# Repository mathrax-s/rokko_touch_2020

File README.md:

# rokko_touch_2020
EAGLE and KiCad files (PSoC4 flexible touch sensor)

</img>

</img>

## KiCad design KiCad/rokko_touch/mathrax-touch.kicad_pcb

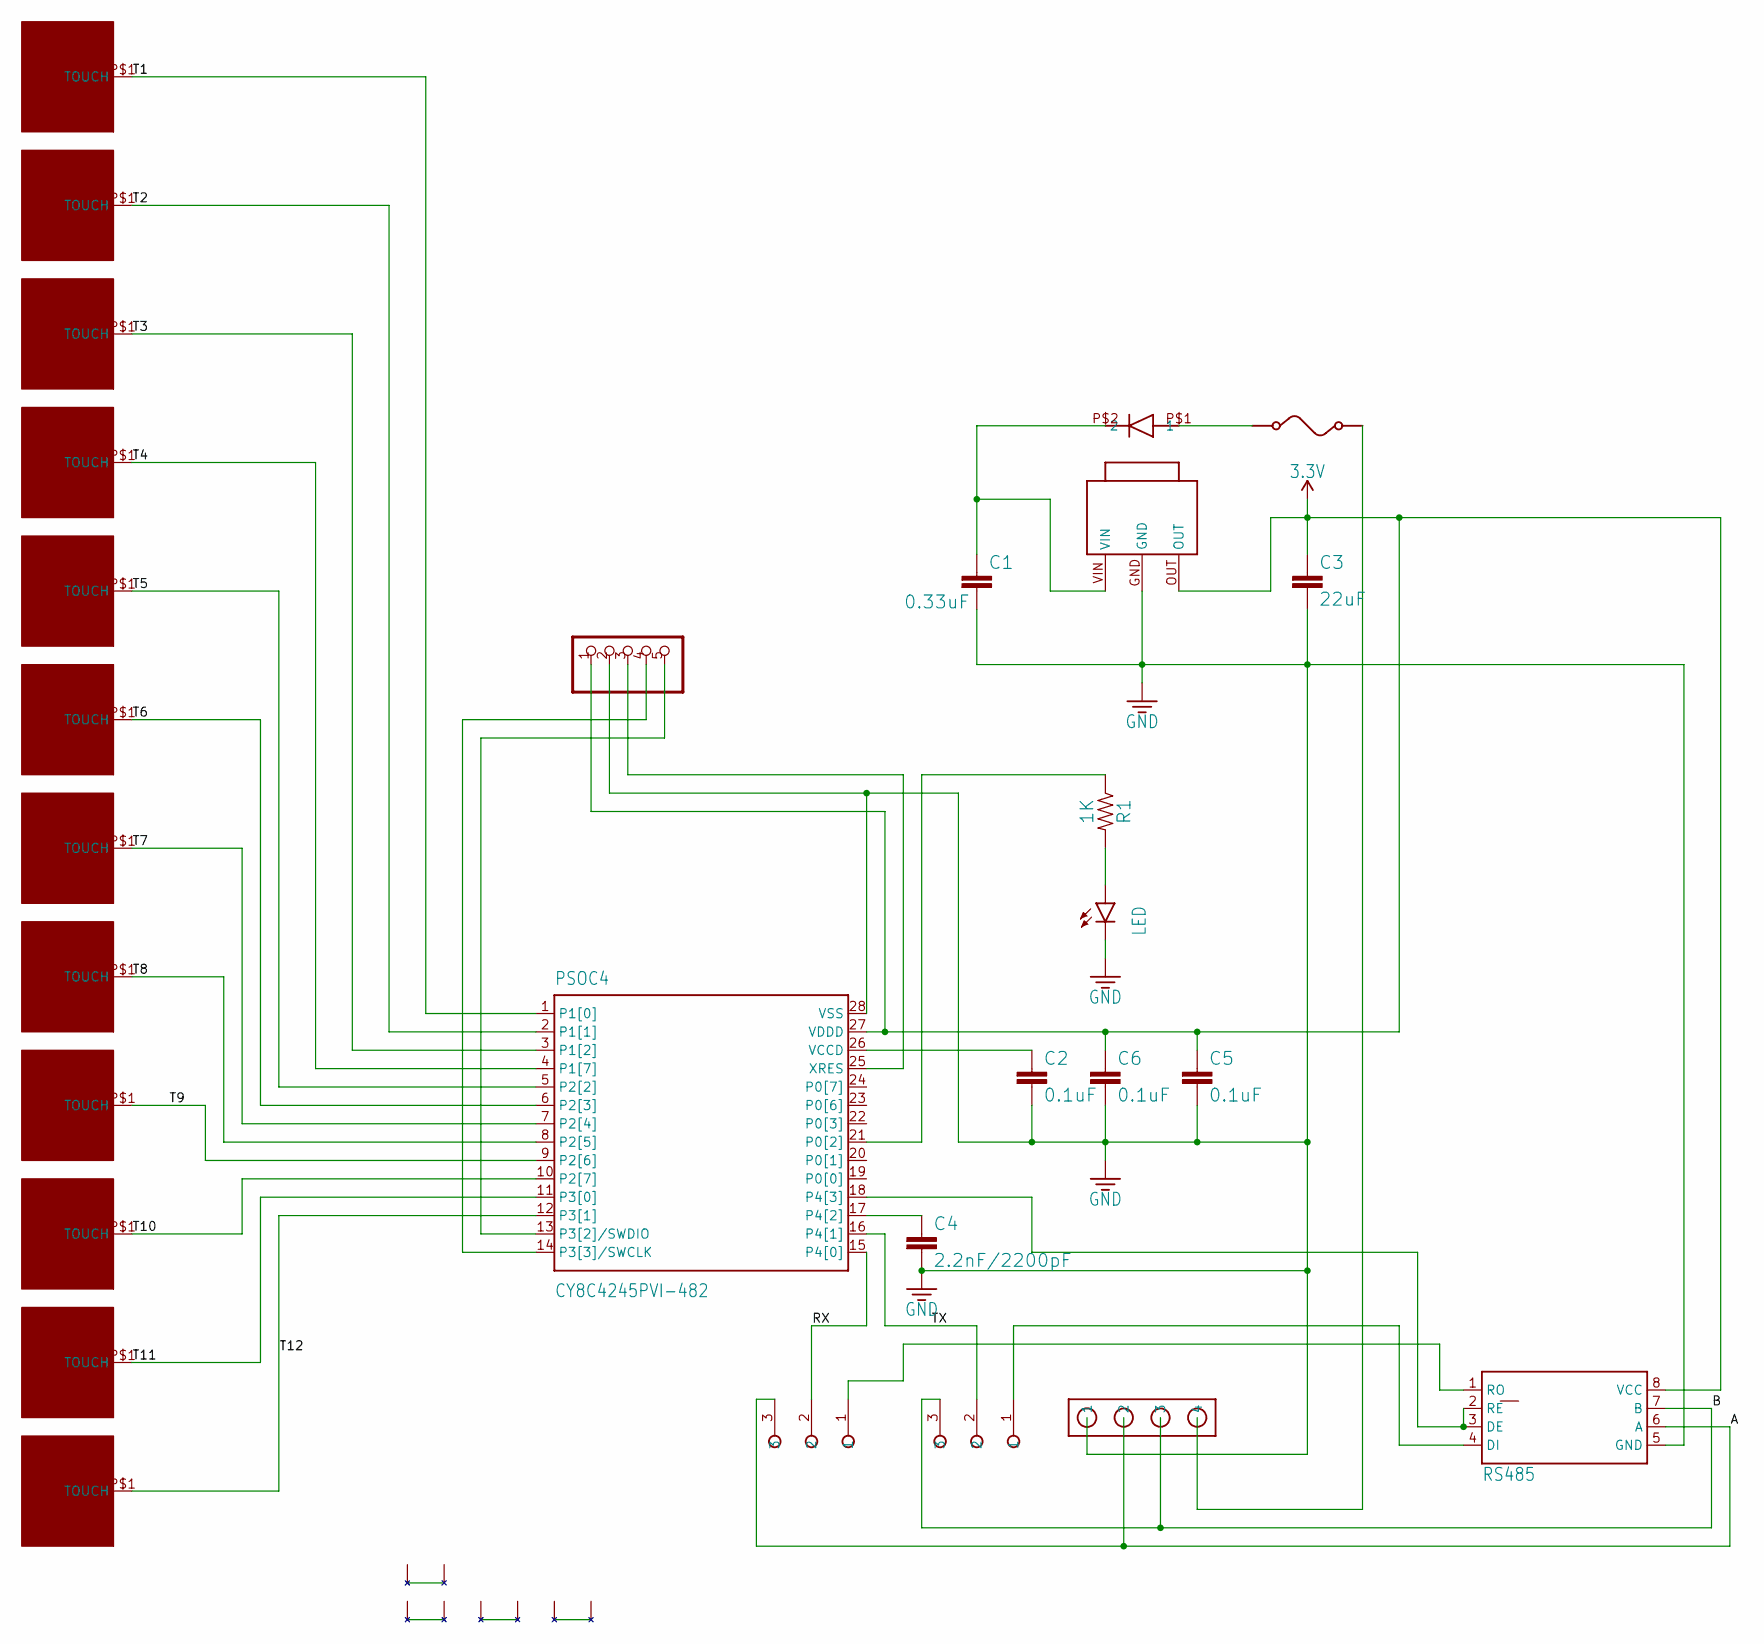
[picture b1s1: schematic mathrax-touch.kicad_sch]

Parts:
C1: 0.33uF; 3216
C2, C5, C6: 0.1uF; 0603
C3: 22uF; 1210
C4: 2.2nF/2200pF; 0603
F1: POLY-SWITCH-HUSE; RESETABLE-HUES
LED0: LED; CHIPLED_0805
PSOC4: CY8C4245PVI-482; SSOP28
R1: 1K; 0603
RS485: RS485; SOIC127P600X175-8N
U$1: PINHEADER-5; PINHEADER-5L
U$2: TOUCH-PTN-3; TOUCH-PTN3
U$3, U$4, U$5, U$6, U$7, U$8, U$9, U$18, U$19, U$20: TOUCH-PTN-2; TOUCH-PTN2
U$11: EH4-UART
U$13: REGULATOR-TO252-3; BA33BC0FP
U$21: TOUCH-PTN-1; TOUCH-PTN1
U$22: DIODE-SS2040L
U$23, U$24: JUMPER
U$25: M-LOGO
U$27: MATHRAX-LOGO

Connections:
3.3V: C3.1, C5.1, C6.1, PSOC4.27 (VDDD), RS485.8 (VCC), U$1.1, U$13.OUT
A: RS485.6 (A), U$11.2, U$24.3
B: RS485.7 (B), U$11.3, U$23.3
CLK: PSOC4.14 (P3[3]/SWCLK), U$1.4
DAT: PSOC4.13 (P3[2]/SWDIO), U$1.5
GND: C1.P$2 (2), C2.2, C3.2, C4.2, C5.2, C6.2, LED0.C, PSOC4.28 (VSS), RS485.5 (GND), U$1.2, U$11.1, U$13.GND
LED: PSOC4.21 (P0[2]), R1.1
unnamed: F1.1, U$22.P$1 (1)
unnamed: U$25.P$1 (1), U$25.P$2 (2)
unnamed: U$27.1, U$27.2
unnamed: U$27.3, U$27.4
unnamed: U$27.5, U$27.6
unnamed: LED0.A, R1.2
unnamed: C4.1, PSOC4.17 (P4[2])
unnamed: C2.1, PSOC4.26 (VCCD)
unnamed: C1.P$1 (1), U$13.VIN, U$22.P$2 (2)
RS485-CE: PSOC4.18 (P4[3]), RS485.2 (RE), RS485.3 (DE)
RST: PSOC4.25 (XRES), U$1.3
RX: PSOC4.15 (P4[0]), U$24.2
RX-485: RS485.1 (RO), U$24.1
T1: PSOC4.1 (P1[0]), U$21.P$1
T2: PSOC4.2 (P1[1]), U$20.P$1
T3: PSOC4.3 (P1[2]), U$19.P$1
T4: PSOC4.4 (P1[7]), U$18.P$1
T5: PSOC4.5 (P2[2]), U$9.P$1
T6: PSOC4.6 (P2[3]), U$8.P$1
T7: PSOC4.7 (P2[4]), U$7.P$1
T8: PSOC4.8 (P2[5]), U$6.P$1
T9: PSOC4.9 (P2[6]), U$5.P$1
T10: PSOC4.10 (P2[7]), U$4.P$1
T11: PSOC4.11 (P3[0]), U$3.P$1
T12: PSOC4.12 (P3[1]), U$2.P$1
TX: PSOC4.16 (P4[1]), U$23.2
TX-485: RS485.4 (DI), U$23.1
VIN: F1.2, U$11.4

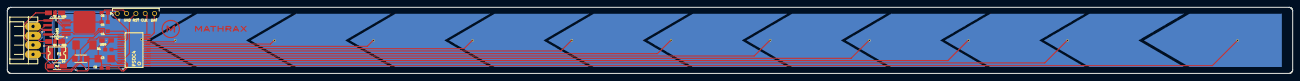
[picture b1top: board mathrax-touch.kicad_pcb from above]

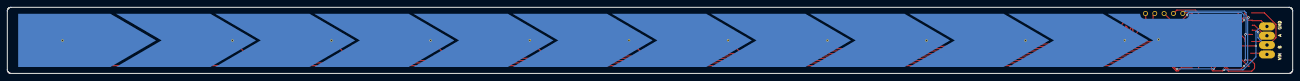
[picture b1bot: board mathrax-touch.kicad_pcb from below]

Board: 2 copper layers, 350.0 x 18.0 mm, 31 parts (12 on the bottom side), 35 nets.

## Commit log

2023-10-26 eagle files
2023-10-26 convert KiCad
2023-10-30 add PSoC4 source
